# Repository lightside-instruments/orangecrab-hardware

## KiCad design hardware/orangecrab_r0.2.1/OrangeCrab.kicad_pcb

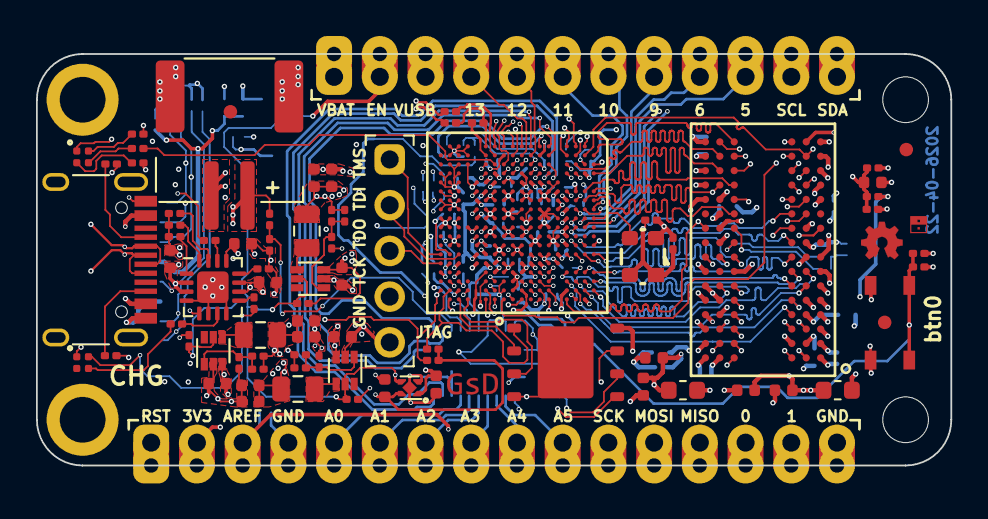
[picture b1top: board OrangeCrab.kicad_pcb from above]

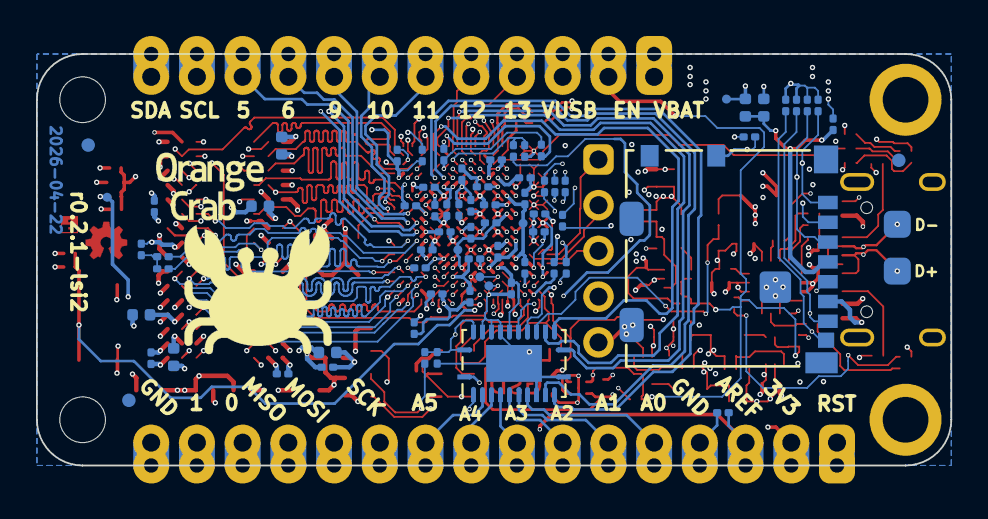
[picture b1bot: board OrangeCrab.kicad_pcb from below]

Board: 6 copper layers, 50.8 x 22.9 mm, 161 parts (74 on the bottom side), 152 nets.

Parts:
C1, C19, C25, C48, C49, C52, C53, C56, C58, C60, C62, C63, C66, C67, C74, C76: 10nF; C_0201_0603Metric
C2, C4, C20, C26, C27, C28, C30, C31, C32, C33, C50, C51, C54, C55, C57, C59, C61, C64, C65, C68, C69, C70, C71, C75: 100nF; C_0201_0603Metric
C3, C21, C22, C34, C35, C36, C37: 1uF; C_0402_1005Metric
C5, C10, C18: 10pF; C_0201_0603Metric
C6, C7, C8, C9, C11, C14, C15, C16, C17, C29: 10uF; C_0402_1005Metric
C12, C13, C46, C47, C77: 4.7uF; C_0402_1005Metric
C23, C24: 22uF; C_0603_1608Metric
D1, D2: LED_ARGB; 0404LED_RGB
FB1, FB2, FB3: 600R; L_0402_1005Metric
FID1, FID2, FID3, FID4, FID5, FID6: Fiducial; Fiducial_0.75mm_Mask1.5mm
H1, H2: MountingHole; MountingHole_2.2mm_M2_Pad
H3, H4: MountingHole; MountingHole_2.1mm
J1: Conn_01x12_Male; Feather_PinHeader_1x12
J2: Conn_01x16_Male; Feather_PinHeader_1x16
J3: USB_C_Receptacle_USB2.0; USB_C_Receptacle_HRO_TYPE-C-31-M-12
J4: MicroSd; molex_microsd_1040310811
J5: JST; JST_PH_B2B-PH-SM4-TB_1x02-1MP_P2.00mm_Vertical
J6: Conn_01x05_Male; PinHeader_1x05_P2.54mm_Vertical
L1, L2, L3: 2.2uH; L_0805_2012Metric
OSC1: KC2520B48.0000C10E00; Oscilator_2.5x2.0
R1, R2: 1k; R_0201_0603Metric
R3, R5, R6, R13, R48, R49, R50, R51: 51R; R_0201_0603Metric
R4, R8, R23, R27, R30, R39: 4.7k; R_0201_0603Metric
R7, R25, R26, R28, R32, R33, R40, R41, R42, R43, R44, R45: 10k; R_0201_0603Metric
R9, R24: 3.57k; R_0201_0603Metric
R10: 56.2k; R_0201_0603Metric
R11: 3.09k; R_0201_0603Metric
R12: 4.32k; R_0201_0603Metric
R14, R16, R46: 5.1k; R_0201_0603Metric
R15, R35: 120k; R_0201_0603Metric
R17: 100k; R_0201_0603Metric
R18, R36: DNP; R_0201_0603Metric
R19: 240R; R_0402_1005Metric
R20, R22, R31: 1.5k; R_0201_0603Metric
R21, R29: 20R; R_0201_0603Metric
R34: 150k; R_0201_0603Metric
R37: 360k; R_0201_0603Metric
R38: 82k; R_0201_0603Metric
SW1: SW_Push; PTS_810_SMT_Switch
TP19, TP20, TP26, TP27, TP29, TP30, TP31, TP32: SMD_TP; TestPoint_Pad_D0.5mm
U1, U2, U7: TLV62569DRL; SOT-563
U3: LFE5U-25F-8MG285C; csBGA285
U4: MT41K64M16TW-107_J-TR; BGA-96_9.0x13.0mm_Layout2x3x16_P0.8mm
U5: BQ24232; QFN-16-1EP_3x3mm_P0.5mm_EP1.75x1.75mm
U6: W25Q128JVP; WSON-8-1EP_6x5mm_P1.27mm_EP3.4x4mm
U9: 74HC4067BQ; Texas_RGY_R-PVQFN-N24_EP2.05x3.1mm
U10: NCP115-2.5; Texas_X2SON-4_1x1mm_P0.65mm
lsi-logo: G***; lsi-logo-no-text-1mm

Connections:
/DRAM/RAM_VDD: C21.1, C23.1, C30.1, C32.1, C34.1, C36.1, FB2.1, U4.B2, U4.D9, U4.G7, U4.K2, U4.K8, U4.N1, U4.N9, U4.R1, U4.R9
/DRAM/RAM_VDDQ: C22.1, C24.1, C31.1, C33.1, C35.1, C37.1, FB3.1, U4.A1, U4.A8, U4.C1, U4.C9, U4.D2, U4.E9, U4.F1, U4.H2, U4.H9
/DRAM/RAM_ZQ: R19.1, U4.L8
/IO/A0: J2.5, R48.1, U9.8
/IO/A1: J2.6, R49.1, U9.7
/IO/A2: J2.7, R50.1, U9.6
/IO/A3: J2.8, R51.1, U9.5
/IO/A4: J2.9, R6.1, U9.4
/IO/A5: J2.10, R3.1, U9.3
/IO/AREF: C71.1, J2.3, U9.2
/IO/_USB_D_N: J3.A7, J3.B7, R29.2, TP27.1
/IO/_USB_D_P: J3.A6, J3.B6, R21.1, TP26.1
ADC_CTRL0: R46.1, U3.G1
ADC_CTRL1: U3.F1, U9.15
ADC_MUX0: U3.F4, U9.10
ADC_MUX1: U3.F3, U9.11
ADC_MUX2: U3.F2, U9.14
ADC_MUX3: U3.H1, U9.13
ADC_SENSE_HI: R44.2, R45.2, U3.H3
ADC_SENSE_LO: C28.1, R46.2, U3.G3
ECP5_VREF: C1.1, C2.1, C3.1, C4.1, C19.1, C20.1, C25.1, C26.1, R1.2, R2.1, U3.B4, U3.C15, U3.H15, U4.H1, U4.M8
EN: J1.2, R18.1, R25.1, R36.1, U1.5, U2.5, U7.5, U10.3
EXT_PLL+: TP19.1, U3.M16
EXT_PLL-: TP20.1, U3.M17
FPGA_RESET: J2.1, R39.1, U3.T15, U3.V17
GND: C1.2, C2.2, C3.2, C4.2, C6.1, C7.1, C8.1, C9.1, C11.1, C12.2, C13.2, C14.1, C15.1, C16.1, C17.1, C19.2, C20.2, C21.2, C22.2, C23.2, C24.2, C25.2, C26.2, C27.2, C28.2, C29.1, C30.2, C31.2, C32.2, C33.2, C34.2, C35.2, C36.2, C37.2, C46.2, C47.2, C48.2, C49.2, C50.2, C51.2, C52.2, C53.2, C54.2, C55.2, C56.2, C57.2, C58.2, C59.2, C60.2, C61.2, C62.2, C63.2, C64.2, C65.2, C66.2, C67.2, C68.2, C69.2, C70.1, C71.2, C74.2, C75.2, C76.2, C77.2, J2.4, J2.16, J3.A1, J3.A12, J3.B1, J3.B12, J3.S1, J4.6, J4.MP, J5.1, J5.MP, J6.5, OSC1.2, R2.2, R9.1, R10.1, R11.1, R12.1, R14.2, R15.2, R16.2, R19.2, R26.1, R27.1, R33.2, R35.2, R38.2, R45.1, SW1.1, U1.2, U2.2, U3.B3, U3.B16, U3.E5, U3.E7, U3.E8, U3.E9, U3.E10, U3.E11, U3.E12, U3.E14, U3.F5, U3.F6, U3.F7, U3.F8, U3.F9, U3.F10, U3.F11, U3.F12, U3.F13, U3.F14, U3.G2, U3.G6, U3.G7, U3.G8, U3.G9, U3.G10, U3.G11, U3.G12, U3.G13, U3.G17, U3.H6, U3.H7, U3.H8, U3.H9, U3.H10, U3.H11, U3.H12, U3.H13, U3.J6, U3.J7, U3.J8, U3.J9, U3.J10, U3.J11, U3.J12, U3.J13, U3.K5, U3.K6, U3.K7, U3.K8, U3.K9, U3.K10, U3.K11, U3.K12, U3.K13, U3.K14, U3.L2, U3.L5, U3.L6, U3.L7, U3.L8, U3.L9, U3.L10, U3.L11, U3.L12, U3.L13, U3.L14, U3.L15, U3.L16, U3.L17, U3.M6, U3.M7, U3.M8, U3.M9, U3.M10, U3.M11, U3.M12, U3.M13, U3.N7, U3.N8, U3.N9, U3.N10, U3.N11, U3.N12, U3.P5, U3.P6, U3.P8, U3.P10, U3.P12, U3.R1, U3.R2, U3.R3, U3.R10, U3.T1, U3.T2, U3.T3, U3.T4, U3.T5, U3.T6, U3.T7, U3.T8, U3.T9, U3.T10, U3.T11, U3.T12, U3.T16, U3.U1, U3.U2, U3.U3, U3.U4, U3.U5, U3.U6, U3.U7, U3.U8, U3.U9, U3.U10, U3.U11, U3.U12, U3.U14, U3.V4, U3.V5, U3.V6, U3.V7, U3.V8, U3.V9, U3.V10, U3.V15, U4.A9, U4.B1, U4.B3, U4.B9, U4.D1, U4.D8, U4.E1, U4.E2, U4.E8, U4.F9, U4.G1, U4.G9, U4.J2, U4.J8, U4.M1, U4.M9, U4.P1, U4.P9, U4.T1, U4.T9, U5.4, U5.6, U5.8, U5.17, U6.4, U7.2, U9.9, U9.12, U9.20, U9.21, U9.22, U10.2
IO_0: J2.14, U3.N17
IO_1: J2.15, U3.M18
IO_5: J1.10, U3.B10
IO_6: J1.9, U3.B9
IO_9: J1.8, U3.C8
IO_10: J1.7, U3.B8
IO_11: J1.6, U3.A8
IO_12: J1.5, U3.H2
IO_13: J1.4, U3.J2
IO_A0: R48.2, U3.L4
IO_A1: R49.2, U3.N3
IO_A2: R50.2, U3.N4
IO_A3: R51.2, U3.H4
IO_A4: R6.2, U3.G4
IO_A5: R3.2, U3.T17
IO_MISO: J2.13, U3.N15
IO_MOSI: J2.12, U3.N16
IO_SCK: J2.11, U3.R17
IO_SCL: J1.11, U3.C9
IO_SDA: J1.12, U3.C10
JTAG_TCK: J6.4, R27.2, U3.U13
JTAG_TDI: J6.2, U3.T13
JTAG_TDO: J6.3, U3.V14
JTAG_TMS: J6.1, U3.V13
LED_B: R24.1, U3.J3
LED_G: R23.1, U3.M3
LED_R: R22.1, U3.K4
unnamed: C5.1, R15.1, R17.1, U1.1
unnamed: C10.1, R34.1, R35.1, U2.1
unnamed: C18.1, R37.1, R38.1, U7.1
unnamed: C27.1, R5.1, R13.1
unnamed: C29.2, C70.2, FB1.1, J4.4
unnamed: D1.2, R22.2
unnamed: D1.3, R23.2
unnamed: D1.4, R24.2
unnamed: D2.2, R8.2
unnamed: D2.3, R7.2
unnamed: J3.A5, R16.1
unnamed: J3.B5, R14.1
unnamed: L1.1, U1.4
unnamed: L2.1, U2.4
unnamed: L3.1, U7.4
unnamed: R7.1, U5.7
unnamed: R8.1, U5.9
unnamed: R9.2, U5.15
unnamed: R10.2, U5.14
unnamed: R11.2, U5.12
unnamed: R12.2, U5.16
unnamed: R26.2, U5.1
unnamed: R32.2, R33.1, U9.16
unnamed: R44.1, U9.1
P1.1V: C5.2, C15.2, C17.2, C48.1, C50.1, C52.1, C54.1, C56.1, C57.1, C58.1, C59.1, C60.1, C61.1, L1.2, R17.2, TP32.1, U3.D8, U3.D9, U3.D10, U3.D11, U3.J4, U3.J5, U3.J14, U3.J15, U3.M4, U3.M15, U3.P7, U3.P9, U3.P11, U9.17
P1.35V: C8.2, C9.2, C10.2, C62.1, C64.1, C66.1, C68.1, FB2.2, FB3.2, L2.2, R1.1, R4.1, R34.2, TP31.1, U3.B18, U3.C6, U3.D17, U3.G5, U3.G14, U3.H5, U3.H14, U3.K15, U3.K16, U3.K17, U3.M14, U3.N14, U9.19
P2.5V: C47.1, C49.1, C51.1, C53.1, C55.1, TP30.1, U3.E6, U3.E13, U3.N6, U3.P13, U9.18, U10.1
P3.3V: C14.2, C16.2, C18.2, C46.1, C63.1, C65.1, C67.1, C69.1, C74.1, C75.1, D1.1, FB1.2, J2.2, J2.e, L3.2, OSC1.1, OSC1.4, R28.1, R30.2, R31.2, R37.2, R39.2, R40.1, R41.1, R42.1, R43.1, TP29.1, U3.D7, U3.D12, U3.M5, U3.N5, U3.N13, U3.P14, U3.T14, U6.8, U9.23, U9.24, U10.4
PUSB_VBUS: C77.1, J1.3, J3.A4, J3.A9, J3.B4, J3.B9, U5.13
QSPI_D2: U3.R18, U6.3
QSPI_D3: U3.N18, U6.7
RAM_A0: U3.C4, U4.N3
RAM_A1: U3.D2, U4.P7
RAM_A2: U3.D3, U4.P3
RAM_A3: U3.A3, U4.N2
RAM_A4: U3.A4, U4.P8
RAM_A5: U3.D4, U4.P2
RAM_A6: U3.C3, U4.R8
RAM_A7: U3.B2, U4.R2
RAM_A8: U3.B1, U4.T8
RAM_A9: U3.D1, U4.R3
RAM_A10: U3.A7, U4.L7
RAM_A11: U3.C2, U4.R7
RAM_A12: U3.B6, U4.N7
RAM_A13: U3.C1, U4.T3
RAM_A14: U3.A2, U4.T7
RAM_A15: U3.C7, U4.M7
RAM_BA0: U3.D6, U4.M2
RAM_BA1: U3.B7, U4.N8
RAM_BA2: U3.A6, U4.M3
RAM_CAS#: U3.D13, U4.K3
RAM_CK+: R5.2, U3.J18, U4.J7
RAM_CK-: R13.2, U3.K18, U4.K7
RAM_CKE: U3.D18, U4.K9
RAM_CS#: U3.A12, U4.L2
RAM_D0: U3.C17, U4.E3
RAM_D1: U3.D15, U4.F7
RAM_D2: U3.B17, U4.F2
RAM_D3: U3.C16, U4.F8
RAM_D4: U3.A15, U4.H3
RAM_D5: U3.B13, U4.H8
RAM_D6: U3.A17, U4.G2
RAM_D7: U3.A13, U4.H7
RAM_D8: U3.F17, U4.D7
RAM_D9: U3.F16, U4.C3
RAM_D10: U3.G15, U4.C8
RAM_D11: U3.F15, U4.C2
RAM_D12: U3.J16, U4.A7
RAM_D13: U3.C18, U4.A2
RAM_D14: U3.H16, U4.B8
RAM_D15: U3.F18, U4.A3
RAM_LDM: U3.G16, U4.E7
RAM_LDQS+: U3.G18, U4.C7
RAM_LDQS-: U3.H17, U4.B7
RAM_ODT: U3.C13, U4.K1
RAM_RAS#: U3.C12, U4.J3
RAM_RESET#: U3.L18, U4.T2
RAM_UDM: U3.D16, U4.D3
RAM_UDQS+: U3.B15, U4.F3
RAM_UDQS-: U3.A16, U4.G3
RAM_WE#: U3.B12, U4.L3
REF_CLK: OSC1.3, U3.A9
SD0_CD: J4.9, R28.2, U3.L1
SD0_CLK: J4.5, U3.K1
SD0_CMD: J4.3, R42.2, U3.K2
SD0_DAT0: J4.7, R41.2, U3.J1
SD0_DAT1: J4.8, R40.2, U3.K3
SD0_DAT2: J4.1, R43.2, U3.L3
SD0_DAT3: J4.2, U3.M1
SPI_CONFIG_MISO: U3.T18, U6.2
SPI_CONFIG_MOSI: U3.U18, U6.5
SPI_CONFIG_SCK: R31.1, U3.U16, U6.6
SPI_CONFIG_SS: R30.1, U3.U17, U6.1
USB_D+: R20.1, R21.2, U3.N1
USB_D-: R29.1, U3.M2
USB_PULLUP: R20.2, U3.N2
USER_BUTTON: C76.1, R4.2, SW1.2, U3.J17
VBATT: C13.1, J1.1, J5.2, R32.1, U5.2, U5.3
VSYS: C6.2, C7.2, C11.2, C12.1, D2.1, R18.2, R25.2, R36.2, U1.3, U2.3, U5.5, U5.10, U5.11, U7.3

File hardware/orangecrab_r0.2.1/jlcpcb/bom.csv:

Comment,Designator,Footprint,JLCPCB Part #（optional）,,,,
10pF,"C5,C10,C18",C_0201_0603Metric,C2991796 ,CL03C100JB3GNNC,Samsung Electro-Mechanics,,
4.7uF,"C12,C13,C46,C47,C77",C_0402_1005Metric,C23733,CL05A475MP5NRNC,Samsung Electro-Mechanics,,
10uF,"C6,C7,C8,C9,C11,C14,C15,C16,C17,C29",C_0402_1005Metric,C315248,CL05A106MP5NUNC,Samsung Electro-Mechanics,,
1uF,"C3,C21,C22,C34,C35,C36,C37",C_0402_1005Metric,C14445,CL05A105KP5NNNC,Samsung Electro-Mechanics,,
22uF,"C23,C24",C_0603_1608Metric,C59461,CL10A226MQ8NRNC,Samsung Electro-Mechanics,,
10nF,"C1,C19,C25,C49,C48,C52,C53,C56,C58,C60,C62,C63,C66,C67,C74,C76",C_0201_0603Metric,C87461,CL03B103KP3NNNC,Samsung Electro-Mechanics,,
100nF,"C2,C4,C20,C26,C27,C28,C30,C31,C32,C33,C50,C51,C54,C55,C57,C59,C61,C64,C65,C68,C69,C70,C71,C75",C_0201_0603Metric,C49062,CL03A104KP3NNNC,Samsung Electro-Mechanics,,
LED_ARGB,"D1,D2",0404LED_RGB,C5752613,R48G-P9Q7-1+R7S5-26+N5P-68-ZB,Osram,,
600R,"FB2,FB3,FB1",L_0402_1005Metric,C76813,MPZ1005S600CT000,TDK,,
MicroSd,J4,molex_microsd_1040310811,C585350,1040310811,MOLEX,,
USB_C_Receptacle_USB2.0,J3,Connector:USB_C_Rec,C167321,USB4105-GF-A,GCT,,
JST,J5,JST_PH_B2B-PH-SM4-TB_1x02-1MP_P2.00mm_Vertical,C295747,S2B-PH-SM4-TB(LF)(SN),JST Commercial,,
Conn_01x05_Male,J6,PinHeader_1x05_P2.54mm_Vertical,,,,,
2.2uH,"L1,L2,L3",L_0805_2012Metric,C86089,LQM21PN2R2NGCD,Murata Electronics,,
KC2520B48.0000C10E00,OSC1,Oscilator_2.5x2.0,C390548,C390534,Seiko Epson,DSC1001CL5-048.0000,Microchip
10k,"R7,R25,R26,R32,R33,R28,R40,R41,R42,R43,R44,R45",R_0201_0603Metric,C106225,RC0201FR-0710KL,YAGEO,,
4.7k,"R8,R23,R4,R30,R39,R27",R_0201_0603Metric,C138135 ,RC0201FR-074K7L,YAGEO,,
1k,"R2,R1",R_0201_0603Metric,C138165,RC0201FR-071KL,YAGEO,,
3.57k,"R9,R24",R_0201_0603Metric,C474659,RC0201FR-073K57L,YAGEO,,
56.2k,R10,R_0201_0603Metric,C327383,RC0201FR-0756K2L,YAGEO,,
3.09k,R11,R_0201_0603Metric,C474645,RC0201FR-073K09L,YAGEO,,
4.32k,R12,R_0201_0603Metric,C474708,RC0201FR-074K32L,YAGEO,,
5.1k,"R14,R16,R46",R_0201_0603Metric,C163490,RC0201JR-075K1L,YAGEO,,
51R,"R3,R6,R5,R13,R48,R50,R51,R49",R_0201_0603Metric,C163499,RC0201FR-0751RL,YAGEO,,
100k,R17,R_0201_0603Metric,C106224,RC0201FR-07100KL,YAGEO,,
DNP,"R18,R36",R_0201_0603Metric,,,,,
240R,R19,R_0402_1005Metric,C137896,RC0402JR-07240RL,YAGEO,,
1.5k,"R20,R22,R31",R_0201_0603Metric,C155737,RC0201FR-071K5L,YAGEO,,
20R,"R21,R29",R_0201_0603Metric,C138113,RC0201JR-0720RL,YAGEO,,
150k,R34,R_0201_0603Metric,C274346 ,RC0201FR-07150KL,YAGEO,,
120k,"R35,R15",R_0201_0603Metric,C274880 ,RC0201JR-07120KL,YAGEO,,
360k,R37,R_0201_0603Metric,C295795,RC0201FR-07360KL,YAGEO,,
82k,R38,R_0201_0603Metric,C273288,RC0201FR-0782KL,YAGEO,,
SW_Push,SW1,PTS_810_SMT_Switch,C221897,PTS810SJK250SMTRLFS,,,
TLV62569DRL,"U1,U2,U7",SOT-563,C163217,TLV62569DRLR,TI,,
NCP115-2.5,U10,Texas_X2SON-4_1x1mm_P0.65mm,C2867028,TLV73325PDQNR,TI,,
LFE5U-85F-8MG285C,U3,csBGA285,C6078773,LFE5U-85F-8MG285C,Lattice,,
MT41K64M16TW-107_J-TR,U4,BGA-96_9.0x13.0mm_Layout2x3x16_P0.8mm,C75475,MT41K64M16TW-107:J,Mikron Tech,,
BQ24232,U5,QFN-16-1EP_3x3mm_P0.5mm_EP1.75x1.75mm,C528622,BQ24232RGTR ,TI,,
W25Q128JVP,U6,WSON-8-1EP_6x5mm_P1.27mm_EP3.4x4mm,C190862,W25Q128JVPIQ,Winbond Elec ,,
74HC4067BQ,U9,Texas_RGY_R-PVQFN-N24_EP2.05x3.1mm,C547033,"74HC4067BQ,118",Nexperia,,

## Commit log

2025-12-26 kicad7 update
2025-12-30 Replaced from ECP5U-25 to ECP5UM-25 pinout and added SerDes banks
2026-01-28 kicad9 update
2026-01-29 Changed min. via diameter from 0.28 to 0.25 mm. Rounded min. trace width to 0.9 mm and DDR3 traces down to 0.1 mm
2026-01-29 Added revision suffix gc1 to indicate the changed layout: 0.2.1-gc1
2026-01-30 0.2.1-gc2: Centered castelated holes to edges and reduced diameter from 1 to 0.8 mm
2026-04-22 0.2.1-li1: Changed the type pads of castellated holes in KiCAD to flag they are castellated holes. Moved version string for better visibility. Added missing USB connector to BOM. Changed from 25F to 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
2026-06-19 0.2.1-lsi2: Added 1 mm 'produced by' mark

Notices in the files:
hardware/orangecrab_r0.2.1/OrangeCrab.kicad_pcb:
Licensed under CERN OHL v.1.2
